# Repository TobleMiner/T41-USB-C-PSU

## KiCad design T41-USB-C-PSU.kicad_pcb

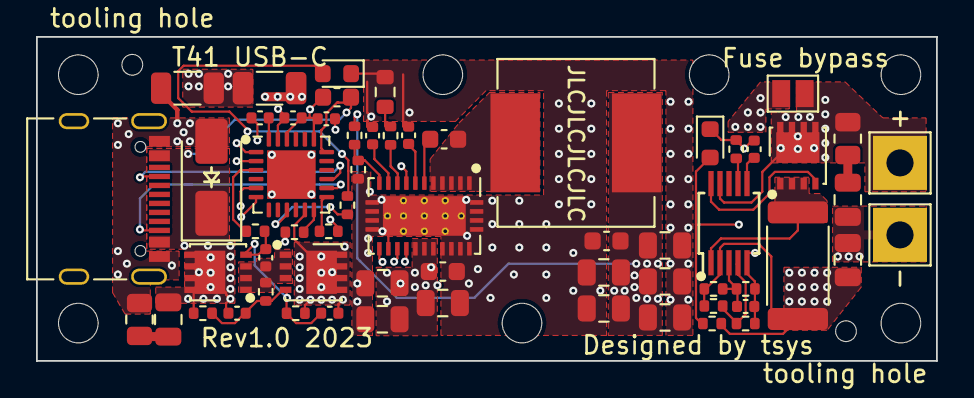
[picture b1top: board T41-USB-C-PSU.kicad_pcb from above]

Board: 4 copper layers, 50.0 x 18.0 mm, 71 parts (0 on the bottom side), 33 nets.

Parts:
C1, C7: 470nF; C_0603_1608Metric
C2, C3, C4, C5, C6: 22uF; C_0805_2012Metric
C8: 100nF HV; C_0603_1608Metric
C9, C10, C11, C14, C20, C26: 10uF; C_0805_2012Metric
C12: 22nF; C_0402_1005Metric
C13: 2.2uF; C_0402_1005Metric
C15: 1nF; C_1206_3216Metric
C16: 1uF HV; C_0603_1608Metric
C17, C18, C21, C27: 1uF; C_0402_1005Metric
C19, C22, C23, C24: 100nF; C_0402_1005Metric
D1: SMAJ22A; D_SMA
D2: RED; LED_0603_1608Metric
D3: GRN; LED_0603_1608Metric
H1, H2: ToolingHole; ToolingHole_JLCSMT
H3, H4, H5, H6, H7, H8, H9: MountingHole; MountingHole_2.2mm_M2
J1: USB_C_Receptacle_USB2.0; USB_C_Receptacle_Palconn_UTC16-G
JP1: Fuse disable; SolderJumper-2_P1.3mm_Open_Pad1.0x1.5mm
L1: 3.3uH; L_Sunlord_MWSA0804S
N1: Housing; Generic_Case
Q1, Q2: AP90P03Q; DFN-8-FET_3x3mm_P0.65mm
Q3: NTTFS4C25NTWG; DFN-8-FET_3x3mm_P0.65mm
R1: 2.2k; R_0402_1005Metric
R2, R20: 33k; R_0402_1005Metric
R3: 36k; R_0603_1608Metric
R4: 2.4k; R_0402_1005Metric
R5, R8, R11, R12: 10k; R_0402_1005Metric
R6, R21: 1R; R_0805_2012Metric
R7: 100k HV; R_1206_3216Metric
R9, R10: 100k; R_0402_1005Metric
R13: 50k; R_0402_1005Metric
R14: 12k; R_0402_1005Metric
R15, R17: 120k; R_0402_1005Metric
R16: 20k; R_0402_1005Metric
R18: 10m; R_2512_6332Metric
R19: 1k; R_0402_1005Metric
TP1: OUT+; TestPoint_THTPad_3.0x3.0mm_Drill1.5mm
TP2: OUT-; TestPoint_THTPad_3.0x3.0mm_Drill1.5mm
U1: LM73606; WQFN-30-4x6mm-EP2.2x4.6mm_P0.5mm
U2: CYPD3177; QFN-24-1EP_4x4mm_P0.5mm_EP2.7x2.7mm
U3: LM5069; MSOP-10_3x3mm_P0.5mm

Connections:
+3V3: C18.1, C19.1, R11.1, R12.1, U2.1 (VBUS_MIN), U2.2 (VBUS_MAX), U2.5 (ISNK_COARSE), U2.23 (VDDD)
/Buck converter/PGOOD: D3.2 (A), R20.2, U1.16 (PGOOD)
/Buck converter/VOUT: C2.1, C3.1, C4.1, C5.1, C6.1, C7.1, C20.1, JP1.1 (A), L1.2, R2.1, R13.1, R15.1, R18.1, R20.1, U1.8 (BIAS), U3.2 (VIN)
/Output protection/OUT: JP1.2 (B), Q3.5 (D), R21.1, TP1.1, U3.9 (OUT)
/USB input/FAULT: R19.1, U2.9 (FAULT)
GND: C2.2, C3.2, C4.2, C5.2, C6.2, C7.2, C8.2, C9.2, C10.2, C11.2, C12.2, C13.2, C15.2, C16.2, C17.2, C18.2, C19.2, C20.2, C24.2, C26.2, C27.2, D1.2 (A2), D2.1 (K), D3.1 (K), J1.A1 (GND), J1.A12 (GND), J1.B1 (GND), J1.B12 (GND), R1.2, R3.1, R6.2, R7.2, R14.2, R16.2, R17.2, TP2.1, U1.12 (PGND), U1.13 (PGND), U1.14 (PGND), U1.15 (PGND), U1.17 (SYNC/MODE), U1.19 (AGND), U1.23 (PGND), U1.24 (PGND), U1.25 (PGND), U1.26 (PGND), U1.27 (PGND), U1.28 (PGND), U1.29 (PGND), U1.30 (PGND), U1.31 (PGND), U2.6 (ISNK_FINE), U2.19 (GND), U2.22 (VSS), U2.25 (GND), U3.5 (GND)
unnamed: C1.1, L1.1, U1.1 (SW), U1.2 (SW), U1.3 (SW), U1.4 (SW), U1.5 (SW)
unnamed: C14.2, R6.1
unnamed: C21.1, Q1.1 (S), Q1.2 (S), Q1.3 (S), Q2.1 (S), Q2.2 (S), Q2.3 (S), R8.1
unnamed: C26.1, R21.2
unnamed: C14.1, C16.1, C22.1, D1.1 (A1), J1.A4 (VBUS), J1.A9 (VBUS), J1.B4 (VBUS), J1.B9 (VBUS), Q1.5 (D), R9.1, U2.18 (VBUS_IN)
unnamed: D2.2 (A), R19.2
unnamed: J1.A5 (CC1), U2.15 (CC1)
unnamed: J1.B5 (CC2), U2.14 (CC2)
unnamed: C15.1, J1.S1 (SHIELD), R7.1
unnamed: C21.2, C22.2, C23.2, Q1.4 (G), Q2.4 (G), R5.1, R8.2, R9.2, R10.2
unnamed: Q3.4 (G), U3.10 (GATE)
unnamed: R3.2, R4.2
unnamed: C1.2, U1.6 (CBOOT)
unnamed: R1.1, R2.2, U1.11 (FB)
unnamed: R4.1, U1.9 (RT)
unnamed: C12.1, U1.10 (SS/TRK)
unnamed: C13.1, U1.7 (VCC)
unnamed: R12.2, U2.13 (HPI_SCL)
unnamed: R11.2, U2.12 (HPI_SDA)
unnamed: R5.2, U2.3 (VBUS_FET_EN)
unnamed: C17.1, U2.24 (VCCD)
unnamed: R15.2, R16.1, U3.4 (OVLO)
unnamed: R17.1, U3.7 (PWR)
unnamed: Q3.1 (S), Q3.2 (S), Q3.3 (S), R18.2, U3.1 (SENSE)
unnamed: C27.1, U3.6 (TIMER)
unnamed: C24.1, R13.2, R14.1, U3.3 (UVLO)
PVIN: C8.1, C9.1, C10.1, C11.1, C23.1, Q2.5 (D), R10.1, U1.18 (EN), U1.20 (PVIN), U1.21 (PVIN), U1.22 (PVIN), U2.11 (VDC_OUT)

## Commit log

2023-09-13 Hide silkscreen designators
2023-09-14 Add 3d models
2023-09-14 Add tooling holes
2023-09-15 Add status LEDs
2023-09-15 Improve VOUT plane connectivity
2023-09-15 Route ISNK to be more easily reachable in case bodging is required
2023-09-15 Fix 33k resistor partnumber
2023-09-15 Use Droid Sans for silkscreen text
2023-11-21 Add case design
2023-11-21 case: add additional interlocking features
2023-11-21 case: add some wiggle room for USB-C port
2023-11-26 Add generic case footprint
2023-11-26 Add cutouts in SLM DFM
2024-03-10 case: increase manufacturing tolerances for JLC3DP SLM process
